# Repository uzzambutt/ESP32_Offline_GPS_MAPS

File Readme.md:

# ESP32-S3 Offline GPS & Map Downloader
**Designed by Muhammad Uzzam Butt [(Contact)](mailto:uzzam@northernstudios.cc) // Made for [HC Offtrack YSWS](https://offtrack.hackclub.com/)**

A hardware-focused project developed for the Hack Club community. This repository contains the complete production-ready hardware design files for a custom 4-layer printed circuit board alongside a local web-based tile extraction tool optimized for generating offline map datasets.

## Hardware Overview

The core of the project is an optimized 4-layer PCB using a multi-rail power distribution network and an isolated RF frontend designed to maintain signal integrity across high-speed digital and highly sensitive analog circuits.

### Circuit Architecture & Subsystems

* **Main Processor:** ESP32-S3-WROOM-1 module hosting the primary system buses, driving peripheral interfaces over SPI/I2C, and featuring an explicit copper keepout zone beneath the onboard PCB antenna to maximize wireless transmission efficiency.
* **GNSS / RF Frontend:** u-blox NEO-M8N positioning engine paired with an onboard U.FL connector for external active or passive antennas. The RF microstrip line is impedance-matched to 50 Ohms with a continuous, unbroken Layer 2 Ground reference plane beneath the entire path to suppress stray noise.
* **Inertial Navigation:** ICM-20948 9-axis IMU integrating a 3-axis gyroscope, 3-axis accelerometer, and 3-axis magnetometer for dead reckoning assistance.
* **Logic Level Translation:** TXS0104 4-bit bidirectional voltage-level translator handling safe high-speed communication between the 1.8V domain of the IMU and the 3.3V native logic level of the ESP32-S3.
* **Power Management Network (PMIC):**
  * **Charging Circuit:** MCP73871 LiPo charge management controller featuring dynamic power path management (System Load Sharing) to seamlessly transition power between USB/DC input and battery power.
  * **System Regulator (3.3V):** TPS63001 high-efficiency buck-boost converter supplying a stable 3.3V rail capable of absorbing the heavy transient current spikes during ESP32 Wi-Fi bursts.
  * **Sensor Regulator (1.8V):** AP2112K-1.8V low-dropout (LDO) linear regulator dedicated exclusively to isolating the sensitive analog components inside the IMU from digital switching noise.
  * **RTC Backup:** CR1220 coin cell retention circuit directly biasing the `V_BCKP` pin of the NEO-M8N to ensure warm/hot start capability and rapid orbital position locks.
* **User Interfaces & Storage:**
  * High-density micro-SD card slot attached via dedicated SPI lines for reading map tiles.
  * Custom TFT display expansion pin header broken out with hardware control lines (`CS`, `DC`, `RST`, `LED`).
  * Supplemental GPIO expansion breakouts (`GPIO7`, `GPIO2`, `GPIO46`, `GPIO45`, `GPIO38`) alongside a dedicated hardware UART interface (`TXD0`/`RXD0`) for diagnostics.

---

## Software: Map Tile Downloader

To support the offline hardware operation, a standalone map utility is provided to extract spatial tiles directly from web tile servers into an indexed directory structure ready for deployment to external storage media.

### Technical Stack
* **Frontend:** HTML, JavaScript, Leaflet.js rendering canvas, Leaflet.draw interface library configured with an orange, dashed polygon utility to visualize map coordinates.
* **Backend:** Python web server powered by the Flask micro-framework utilizing standard math libraries to translate mercator coordinates into standard XYZ tile grids.
* **Data Provider:** CartoDB Voyager raster tile api.

### Installation & Operation

1. Navigate to the code directory containing the script assets.
2. Install the necessary networking dependencies via pip:
   ```
   pip install flask requests

 3. Initialize the local Flask loop:
   ```
   python app.py
   
   ```
 4. Point a web browser to http://127.0.0.1:5000.
 5. Use the rectangle bounding tool to drag a perimeter over the geographical region you want to download.
 6. Trigger the download pipeline; files are compiled directly into the root folder under
    ```
    /downloaded_maps/{zoom}/{x}/{y}.png
    ```

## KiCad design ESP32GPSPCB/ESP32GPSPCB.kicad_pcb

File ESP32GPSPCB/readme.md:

just adding it here temporarily to sync hackatime with it!

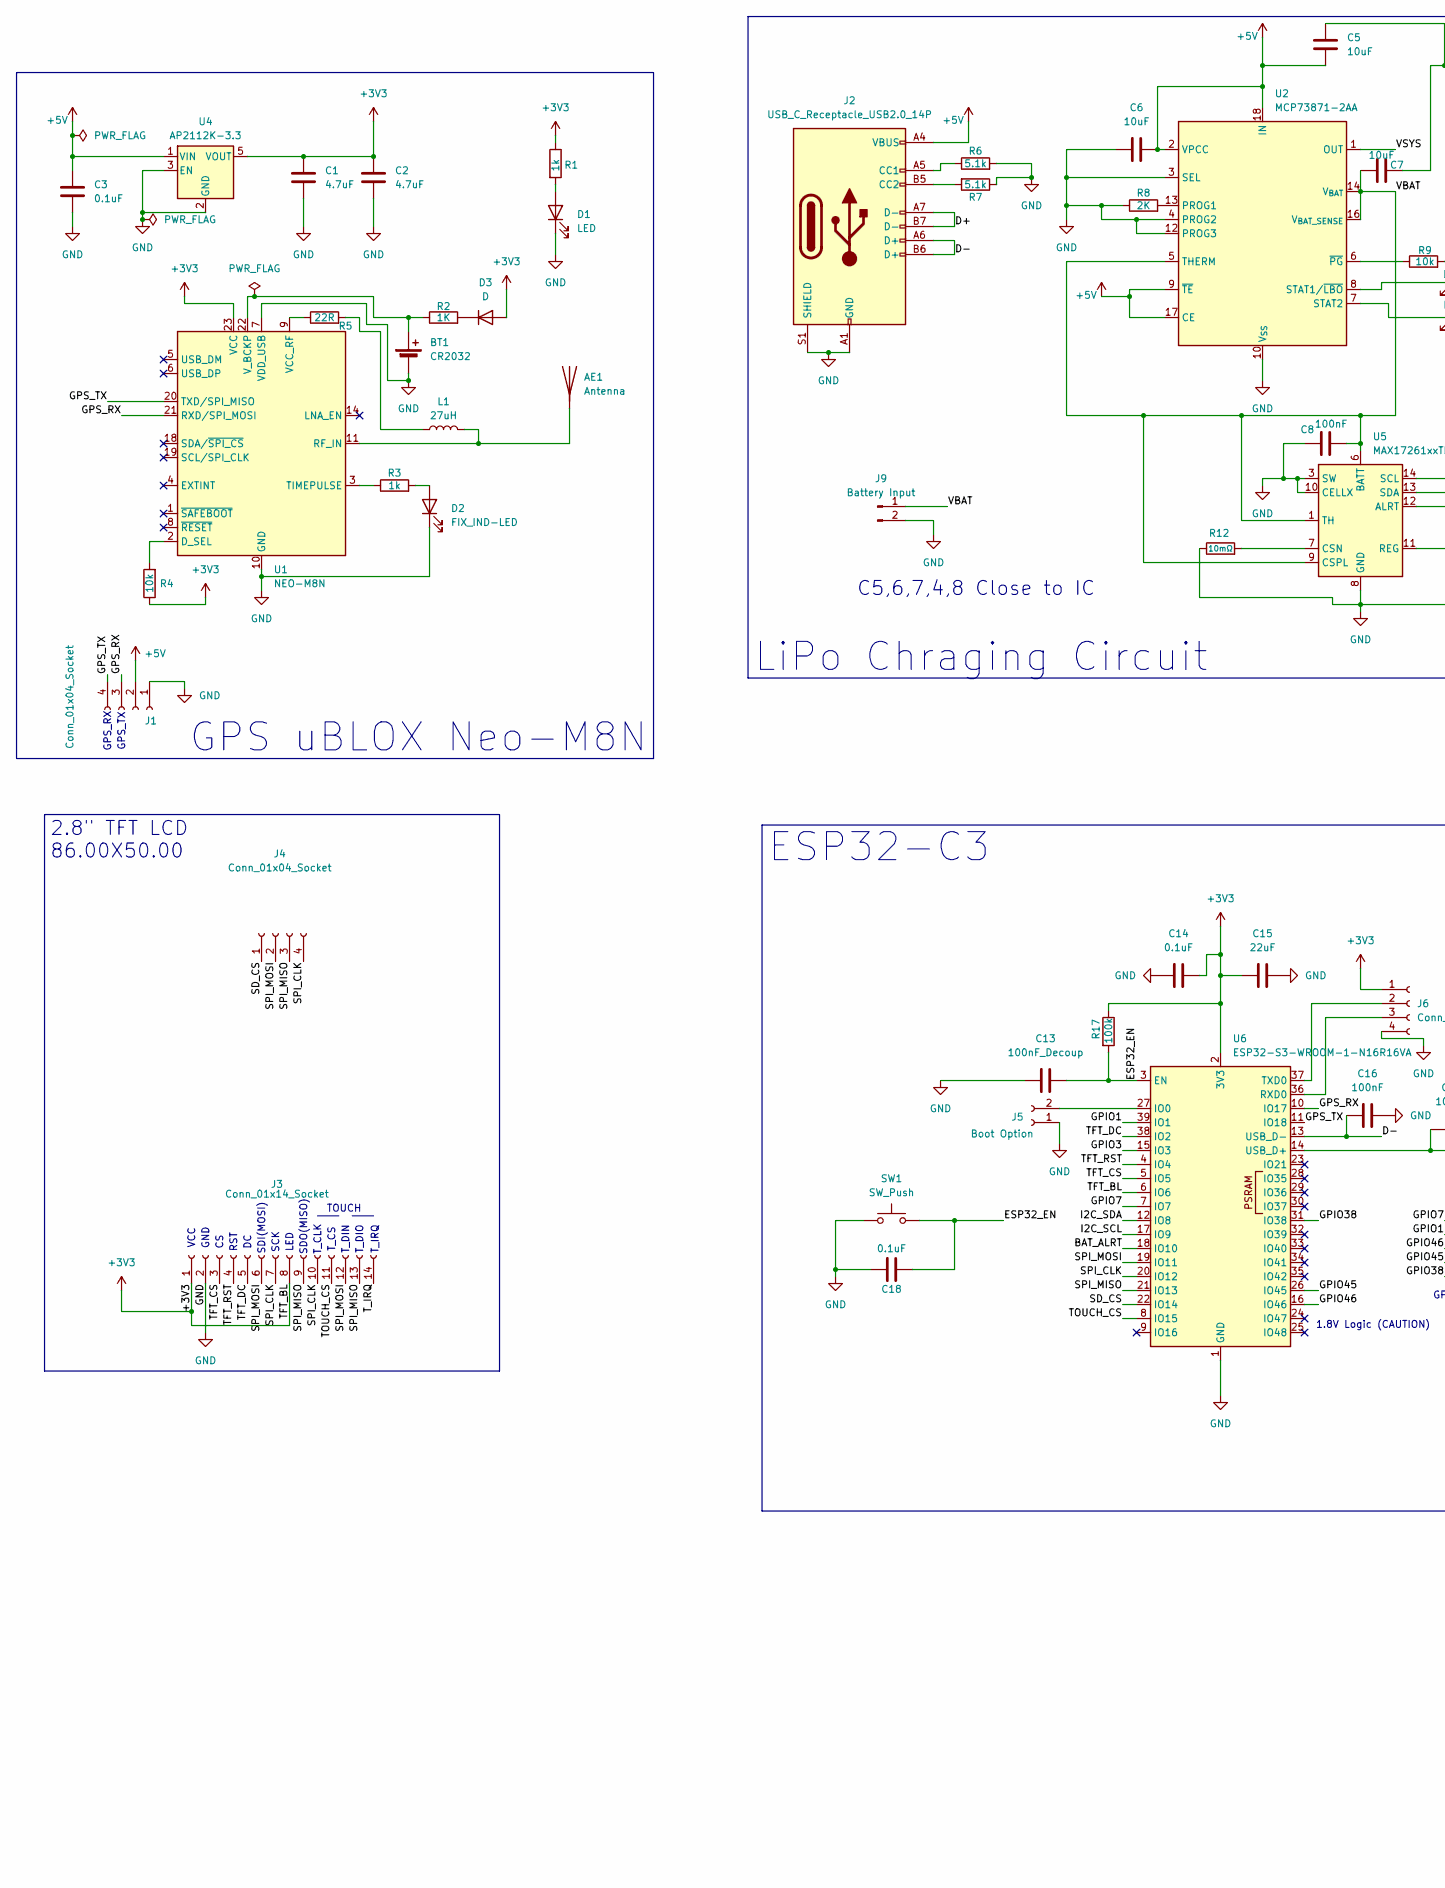
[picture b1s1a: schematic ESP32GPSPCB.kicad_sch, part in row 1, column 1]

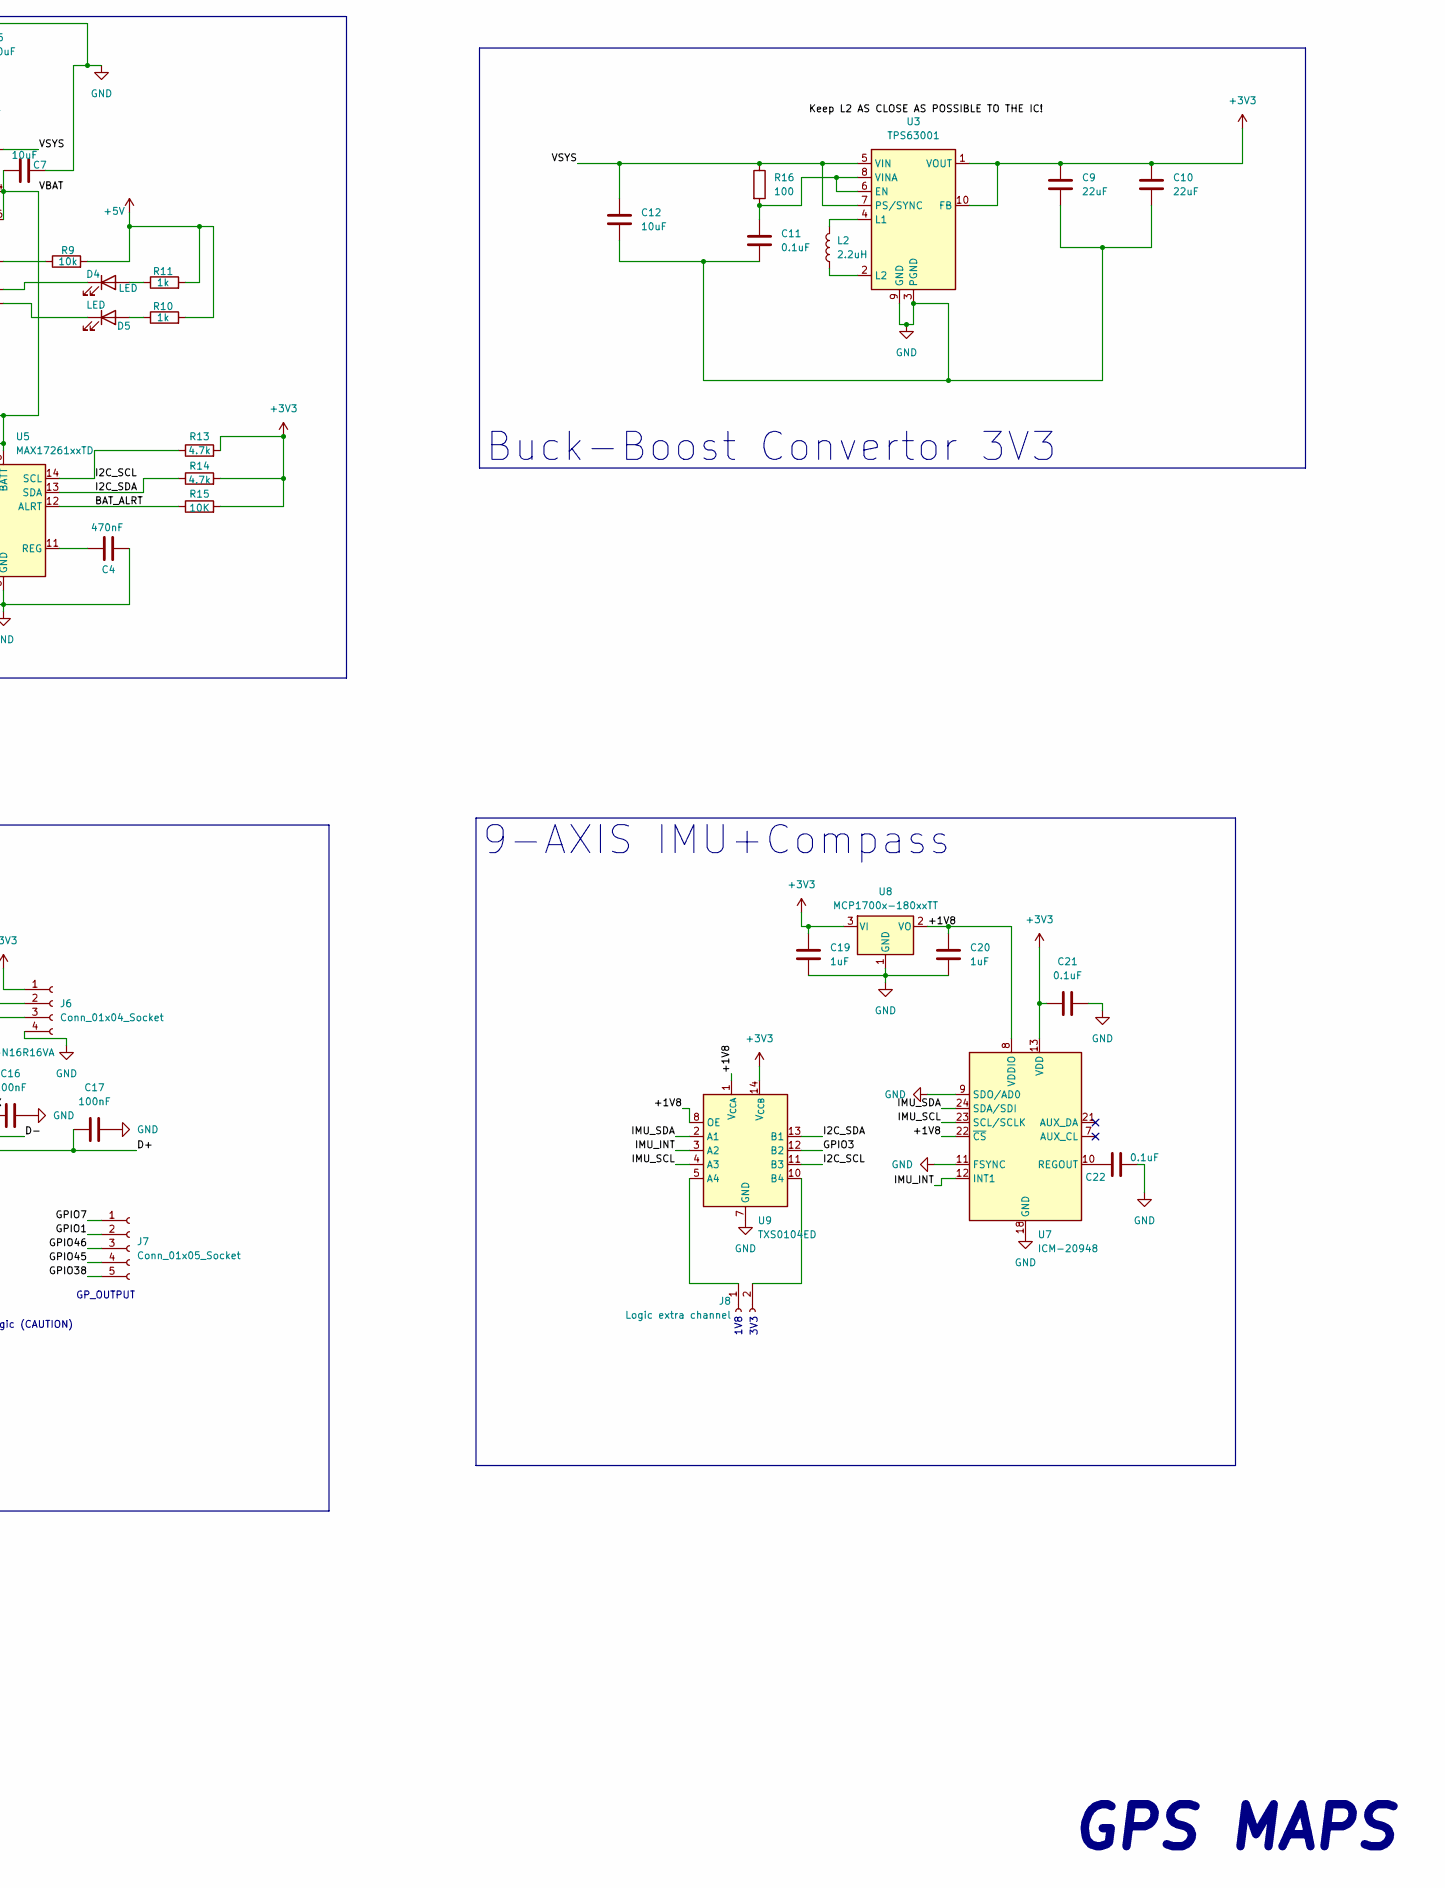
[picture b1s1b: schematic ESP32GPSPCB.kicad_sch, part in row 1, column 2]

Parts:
AE1: Antenna; U.FL_Hirose_U.FL-R-SMT-1_Vertical
BT1: CR2032; BatteryHolder_Keystone_500
C1, C2: 4.7uF; C_0805_2012Metric
C3: 0.1uF; C_0805_2012Metric
C4: 470nF; C_0603_1608Metric
C5, C6, C7, C12: 10uF; C_0603_1608Metric
C8, C16, C17: 100nF; C_0603_1608Metric
C9, C10: 22uF; C_0805_2012Metric
C11, C14: 0.1uF; C_0603_1608Metric
C13: 100nF_Decoup; C_0402_1005Metric
C15: 22uF; C_0603_1608Metric
C18, C21, C22: 0.1uF; C_0402_1005Metric
C19, C20: 1uF; C_0603_1608Metric
D1: LED; LED_0402_1005Metric
D2: FIX_IND-LED; LED_0805_2012Metric
D3: D; D_0603_1608Metric
D4, D5: LED; LED_0805_2012Metric
J1, J4, J6: Conn_01x04_Socket; PinHeader_1x04_P2.54mm_Vertical
J2: USB_C_Receptacle_USB2.0_14P; USB_C_Receptacle_HCTL_HC-TYPE-C-16P-01A
J3: Conn_01x14_Socket; PinHeader_1x14_P2.54mm_Vertical
J5: Boot Option; PinHeader_1x02_P2.54mm_Vertical
J7: Conn_01x05_Socket; PinHeader_1x05_P2.54mm_Vertical
J8: Logic extra channel; PinHeader_1x02_P2.54mm_Vertical
J9: Battery Input; JST_PH_B2B-PH-K_1x02_P2.00mm_Vertical
L1: 27uH; L_0603_1608Metric
L2: 2.2uH; L_0402_1005Metric
R1, R3, R10, R11: 1k; R_0402_1005Metric
R2: 1K; R_0402_1005Metric
R4, R9: 10k; R_0402_1005Metric
R5: 22R; R_0402_1005Metric
R6, R7: 5.1k; R_0402_1005Metric
R8: 2K; R_0402_1005Metric
R12: 10mΩ; R_0402_1005Metric
R13, R14: 4.7k; R_0402_1005Metric
R15: 10K; R_0402_1005Metric
R16: 100; R_0402_1005Metric
R17: 100k; R_0603_1608Metric
SW1: SW_Push; SW_Push_1P1T_NO_CK_KMR2
U1: NEO-M8N; ublox_NEO
U2: MCP73871-2AA; QFN-20-1EP_4x4mm_P0.5mm_EP2.5x2.5mm
U3: TPS63001; Texas_DRC0010J_ThermalVias
U4: AP2112K-3.3; SOT-23-5
U5: MAX17261xxTD; TDFN-14-1EP_3x3mm_P0.4mm_EP1.78x2.35mm
U6: ESP32-S3-WROOM-1-N16R16VA; ESP32-S3-WROOM-1
U7: ICM-20948; InvenSense_QFN-24_3x3mm_P0.4mm
U8: MCP1700x-180xxTT; SOT-23
U9: TXS0104ED; SOIC-14_3.9x8.7mm_P1.27mm

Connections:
+3V3: C1.1, C2.1, C9.1, C10.1, C14.2, C15.1, C19.1, C21.1, D3.2 (A), J3.1, J3.8, J6.1, R1.1, R4.1, R13.2, R14.2, R15.2, R17.1, U1.23 (VCC), U3.1 (VOUT), U3.10 (FB), U4.5 (VOUT), U6.2 (3V3), U6.6 (IO6), U7.13 (VDD), U8.3 (VI), U9.14 (V_{CCB})
+5V: C3.1, C5.2, C6.2, J1.2, J2.A4 (VBUS), J2.A9 (VBUS), J2.B4 (VBUS), J2.B9 (VBUS), R9.2, R10.2, R11.2, U2.2 (VPCC), U2.9 (~TE), U2.17 (CE), U2.18 (IN), U2.19 (IN), U4.1 (VIN)
/+1V8: C20.1, U7.8 (VDDIO), U7.22 (~CS), U8.2 (VO), U9.1 (V_{CCA}), U9.8 (OE)
/BAT_ALRT: R15.1, U5.12 (ALRT), U6.18 (IO10)
/D+: C17.1, J2.A7 (D-), J2.B7 (D-), U6.14 (USB_D+)
/D-: C16.1, J2.A6 (D+), J2.B6 (D+), U6.13 (USB_D-)
/ESP32_EN: C13.2, C18.1, R17.2, SW1.2, U6.3 (EN)
/GPIO1: J7.2, U6.39 (IO1)
/GPIO3: U6.15 (IO3), U9.12 (B2)
/GPIO7: J7.1, U6.7 (IO7)
/GPIO38: J7.5, U6.31 (IO38)
/GPIO45: J7.4, U6.26 (IO45)
/GPIO46: J7.3, U6.16 (IO46)
/GPS_RX: J1.3, U1.21 (RXD/SPI_MOSI), U6.10 (IO17)
/GPS_TX: J1.4, U1.20 (TXD/SPI_MISO), U6.11 (IO18)
/I2C_SCL: R13.1, U5.14 (SCL), U6.17 (IO9), U9.11 (B3)
/I2C_SDA: R14.1, U5.13 (SDA), U6.12 (IO8), U9.13 (B1)
/IMU_INT: U7.12 (INT1), U9.3 (A2)
/IMU_SCL: U7.23 (SCL/SCLK), U9.4 (A3)
/IMU_SDA: U7.24 (SDA/SDI), U9.2 (A1)
/SD_CS: J4.1, U6.22 (IO14)
/SPI_CLK: J3.7, J3.10, J4.4, U6.20 (IO12)
/SPI_MISO: J3.9, J3.13, J4.3, U6.21 (IO13)
/SPI_MOSI: J3.6, J3.12, J4.2, U6.19 (IO11)
/TFT_CS: J3.3, U6.5 (IO5)
/TFT_DC: J3.5, U6.38 (IO2)
/TFT_RST: J3.4, U6.4 (IO4)
/TOUCH_CS: J3.11, U6.8 (IO15)
/T_IRQ: J3.14
/VBAT: C7.1, C8.2, J9.1, U2.5 (THERM), U2.14 (V_{BAT}), U2.15 (V_{BAT}), U2.16 (V_{BAT_SENSE}), U5.1 (TH), U5.6 (BATT), U5.9 (CSPL)
/VSYS: C12.1, R16.1, U2.1 (OUT), U2.20 (OUT), U3.5 (VIN), U3.7 (PS/SYNC)
GND: BT1.2 (-), C1.2, C2.2, C3.2, C4.2, C5.1, C6.1, C7.2, C8.1, C9.2, C10.2, C11.2, C12.2, C13.1, C14.1, C15.2, C16.2, C17.2, C18.2, C19.2, C20.2, C21.2, C22.2, D1.1 (K), D2.1 (K), J1.1, J2.A1 (GND), J2.A12 (GND), J2.B1 (GND), J2.B12 (GND), J2.S1 (SHIELD), J3.2, J5.1, J6.4, J9.2, R6.2, R7.1, R8.1, R12.1, SW1.1, U1.7 (VDD_USB), U1.10 (GND), U1.12 (GND), U1.13 (GND), U1.24 (GND), U2.3 (SEL), U2.4 (PROG2), U2.10 (V_{SS}), U2.11 (V_{SS}), U2.12 (PROG3), U2.21 (V_{SS}), U3.3 (PGND), U3.9 (GND), U3.11 (PGND), U4.2 (GND), U4.3 (EN), U5.3 (SW), U5.8 (GND), U5.10 (CELLX), U5.15 (GND), U6.1 (GND), U6.40 (GND), U6.41 (GND), U7.9 (SDO/AD0), U7.11 (FSYNC), U7.18 (GND), U7.20 (GND), U8.1 (GND), U9.7 (GND)
unnamed: AE1.1 (A), L1.2, U1.11 (RF_IN)
unnamed: BT1.1 (+), R2.1, U1.22 (V_BCKP)
unnamed: D1.2 (A), R1.2
unnamed: D2.2 (A), R3.2
unnamed: D3.1 (K), R2.2
unnamed: D4.2 (A), R11.1
unnamed: D4.1 (K), U2.8 (STAT1/~LBO)
unnamed: D5.2 (A), R10.1
unnamed: D5.1 (K), U2.7 (STAT2)
unnamed: J2.A5 (CC1), R6.1
unnamed: J2.B5 (CC2), R7.2
unnamed: J5.2, U6.27 (IO0)
unnamed: J6.2, U6.37 (TXD0)
unnamed: J6.3, U6.36 (RXD0)
unnamed: J8.1, U9.5 (A4)
unnamed: J8.2, U9.10 (B4)
unnamed: L1.1, R5.2
unnamed: R4.2, U1.2 (D_SEL)
unnamed: R3.1, U1.3 (TIMEPULSE)
unnamed: R5.1, U1.9 (VCC_RF)
unnamed: R8.2, U2.13 (PROG1)
unnamed: R9.1, U2.6 (~PG)
unnamed: C11.1, R16.2, U3.6 (EN), U3.8 (VINA)
unnamed: L2.2, U3.4 (L1)
unnamed: L2.1, U3.2 (L2)
unnamed: R12.2, U5.7 (CSN)
unnamed: C4.1, U5.11 (REG)
unnamed: C22.1, U7.10 (REGOUT)

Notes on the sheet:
TOUCH
3V3
GP_OUTPUT
T_IRQ
RST
T_DIO
T_DIN
VCC
C5,6,7,4,8 Close to IC
SDI(MOSI)
GPS_TX
1V8
SDO(MISO)
LED
GPS MAPS
GND
SCK
GPS_RX
T_CS
1.8V Logic (CAUTION)
T_CLK
Buck-Boost Convertor 3V3
ESP32-C3
2.8" TFT LCD 86.00X50.00
9-AXIS IMU+Compass
LiPo Chraging Circuit
GPS uBLOX Neo-M8N

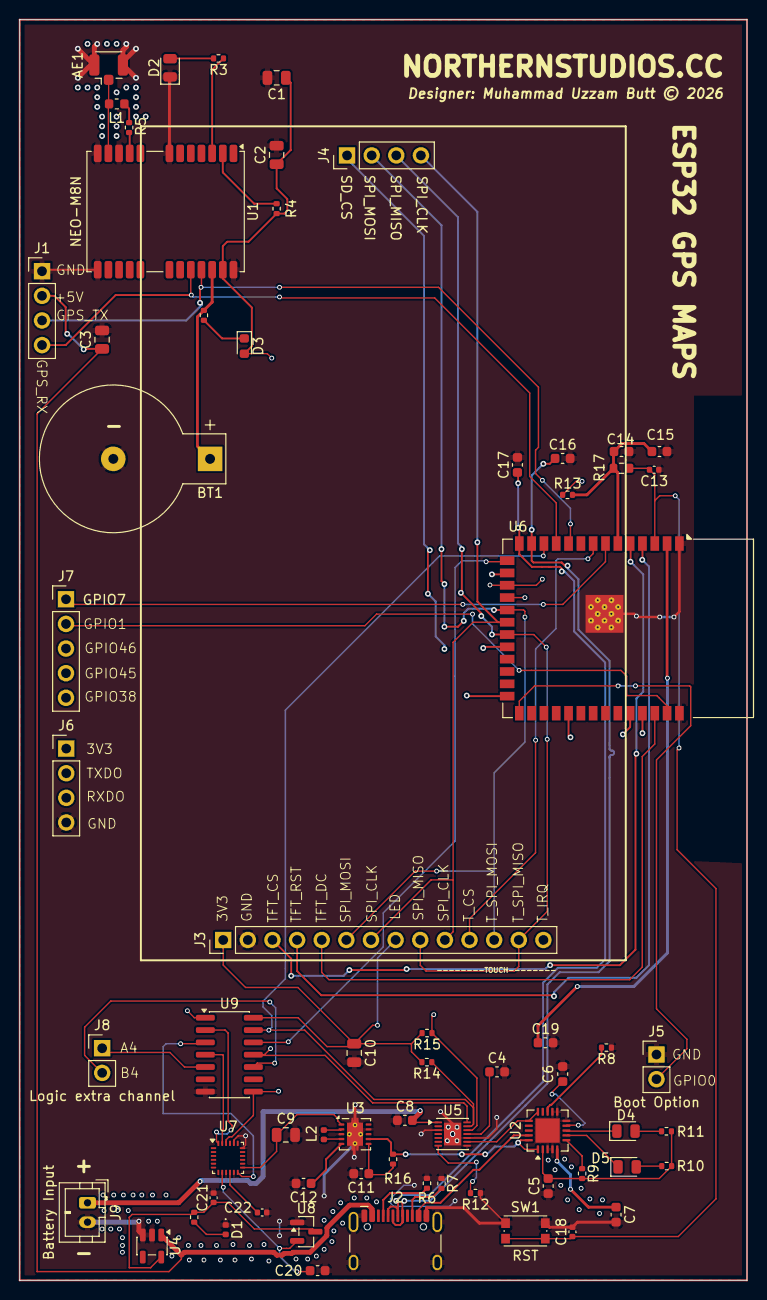
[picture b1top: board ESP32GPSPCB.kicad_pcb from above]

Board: 4 copper layers, 75.0 x 130.0 mm, 67 parts (0 on the bottom side), 59 nets.

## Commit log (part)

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2026-06-10 completed GPS and BUCK-BOOST CONV
2026-06-11 fixed some stuff
2026-06-11 started working on the ESP32 chip
2026-06-12 completed ESP32 logic, wired up some net labels and stuff
2026-06-12 completed IMU circuit, added logic level convertor
2026-06-12 centered
2026-06-12 schematic added, IMU finished, ERC RAN ERRORS FIXED
2026-06-16 placed all components
2026-06-16 routed some of the parts
2026-06-18 Routed all traces and poured copper planes, GND, +1V8, VSYS, +3V3
2026-06-18 added designs and silkscreens
2026-06-18 power plane fixes
2026-06-19 started working on code

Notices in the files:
ESP32GPSPCB/ESP32GPSPCB.kicad_pcb:
Designer: Muhammad Uzzam Butt ©️ 2026
Readme.md:
License: MIT
